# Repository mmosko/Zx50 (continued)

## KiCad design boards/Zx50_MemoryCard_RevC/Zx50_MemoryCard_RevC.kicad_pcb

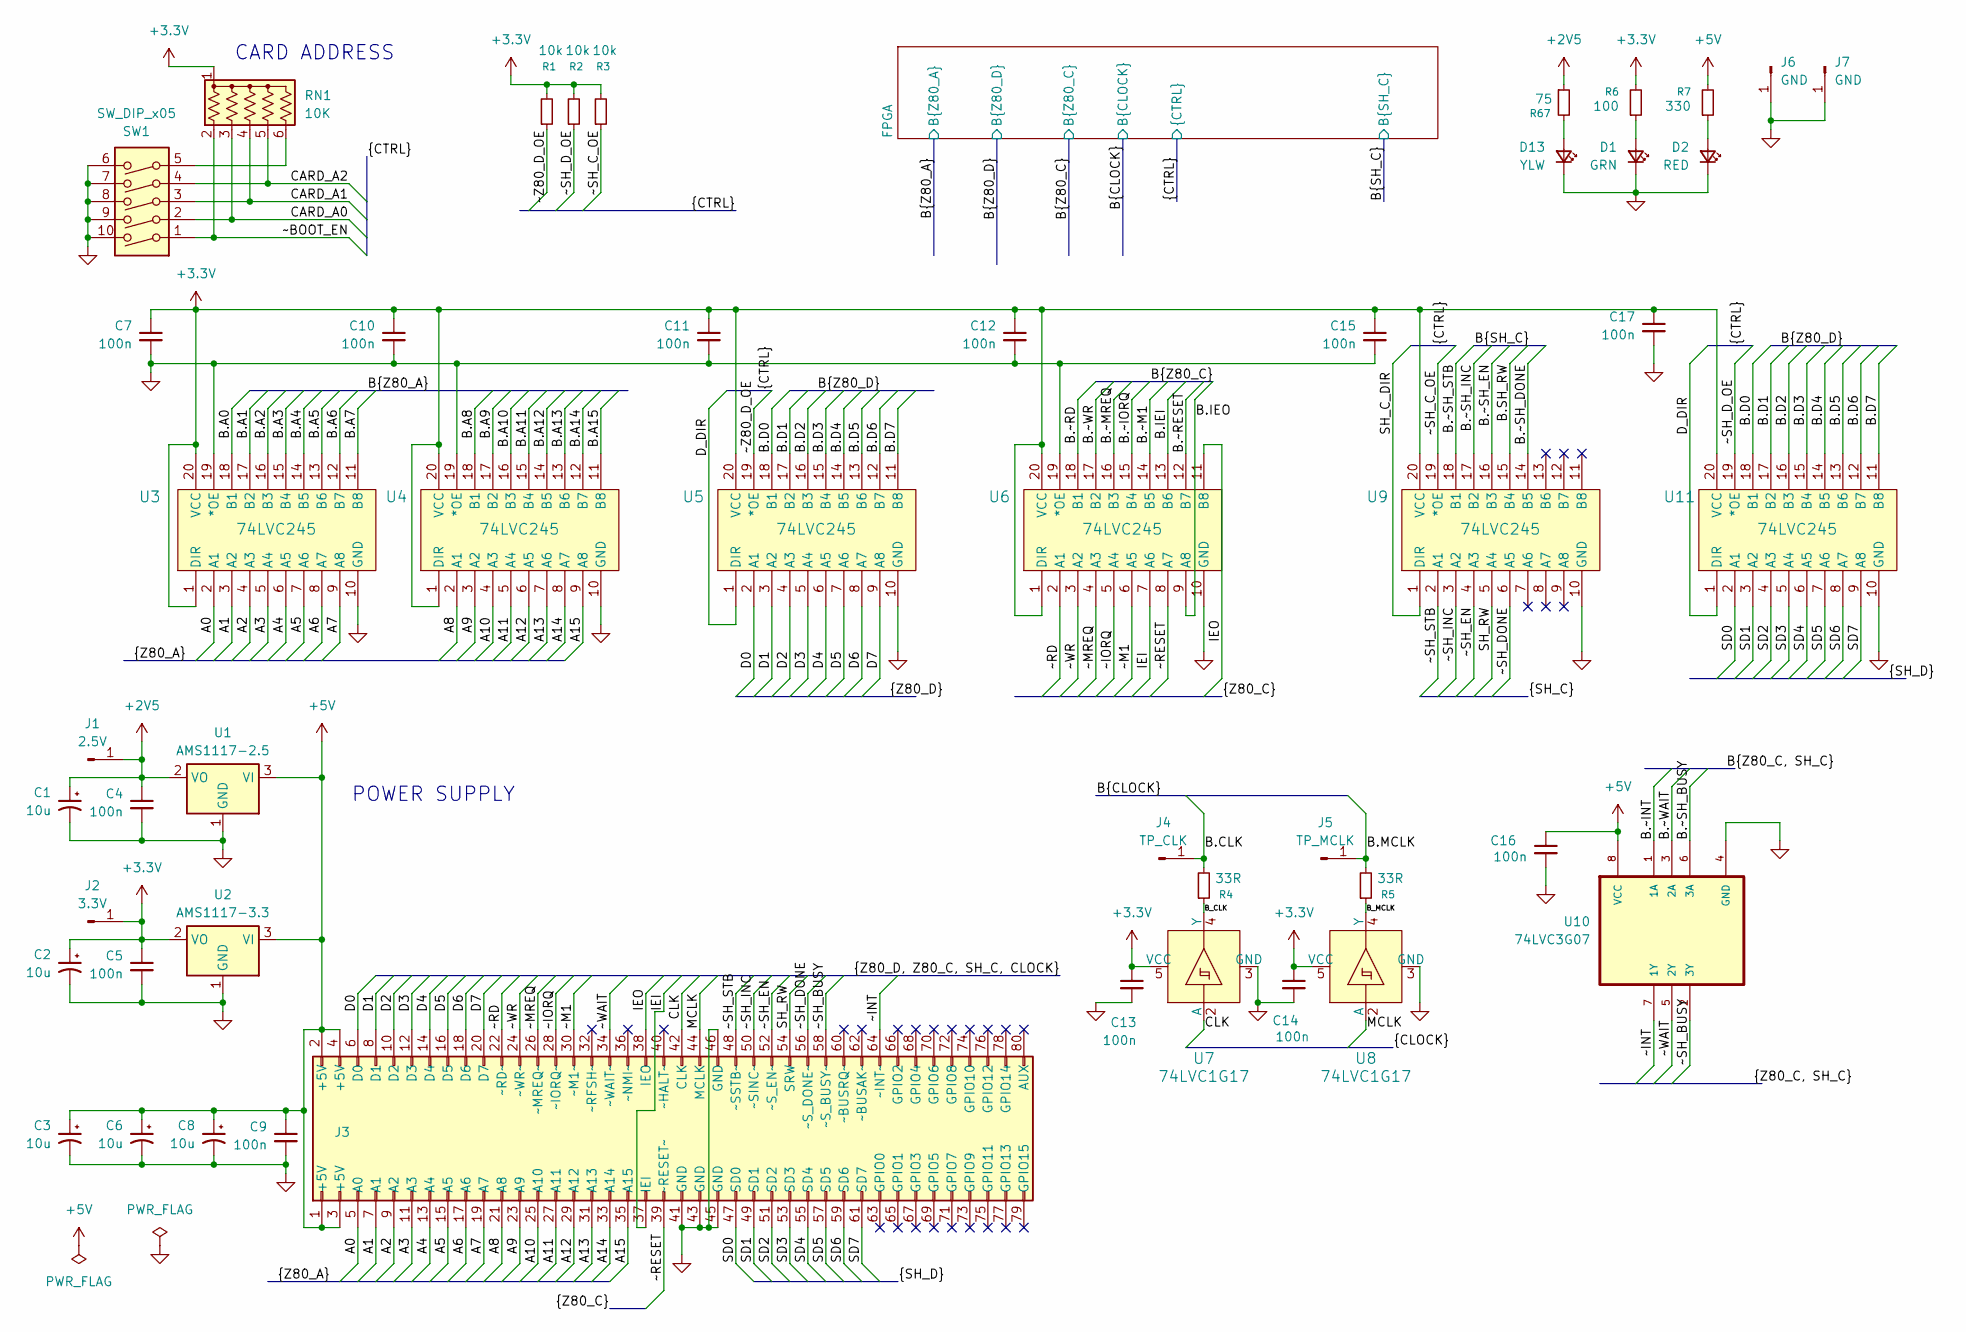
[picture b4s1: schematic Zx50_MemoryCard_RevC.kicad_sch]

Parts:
C1, C2, C3, C6, C8: 10u; C_1206_3216Metric; MFG PN AVX TAJA106K016RNJ Tantalinium; LCSC C7171
C4, C5, C7, C9, C10, C11, C12, C13, C14, C15, C16, C17: 100n; C_0402_1005Metric; LCSC C1525
D1: GRN; LED_0805_2012Metric; MFG_PN KT-0805G; LCSC C2297
D2: RED; LED_0805_2012Metric; MFG_PN NCD0805R1; LCSC C84256
D13: YLW; LED_0805_2012Metric; MFG_PN KT-0805G; LCSC C2297
J1: 2.5V; PinHeader_1x01_P2.54mm_Vertical
J2: 3.3V; PinHeader_1x01_P2.54mm_Vertical
J3: Zx50_EdgeConnector; PinSocket_2x40_P2.54mm_Horizontal_Edge; DigiKey_PN 2057-PH2RA-80-UA-ND
J4: TP_CLK; PinHeader_1x01_P2.54mm_Vertical
J5: TP_MCLK; PinHeader_1x01_P2.54mm_Vertical
J6, J7: GND; PinHeader_1x01_P2.54mm_Vertical
R1, R2, R3: 10k; R_0805_2012Metric; MFG_PN 0805W8F1002T5E; LCSC C17414
R4, R5: 33R; R_0603_1608Metric; MFG_PN 0603WAF330JT5E; LCSC C23140
R6: 100; R_0805_2012Metric; MFG_PN 0805W8F1000T5E; LCSC C17408
R7: 330; R_0805_2012Metric; MFG_PN 0805W8F3300T5E; LCSC C17630
R67: 75; R_0603_1608Metric; MFG_PN 0603WAF750JT5E; LCSC C4275
RN1: 10K; R_Array_SIP6; LCSC 4606X-AP1-103LF
SW1: SW_DIP_x05; SW_DIP_SPSTx05_Slide_9.78x14.88mm_W7.62mm_P2.54mm; LCSC 208-5
U1: AMS1117-2.5; SOT-223-3_TabPin2; Mouser_PN 926-LM1117MPX2.5NOPB
U2: AMS1117-3.3; SOT-223-3_TabPin2; Mouser_PN 926-LM1117MPX3.3NOPB
U3, U4, U5, U6, U9, U11: 74LVC245; TSSOP-20_4.4x6.5mm_P0.65mm; MFG_PART SN74LVC245APWR; LCSC C7848
U7, U8: 74LVC1G17; SOT-753; MPN SN74LVC1G17DBVR; Digi-Key_PN 296-11933-1-ND
U10: 74LVC3G07; VSSOP-8_2.3x2mm_P0.5mm; MFG_PN SN74LVC3G07DCUR; LCSC C131955

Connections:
+2V5: C1.1, C4.1, J1.1, R67.1, U1.2 (VO); also elsewhere on the board
+3.3V: C2.1, C5.1, C7.1, C10.1, C11.1, C12.1, C13.1, C14.1, C15.1, C17.1, J2.1, R1.2, R2.2, R3.2, R6.2, RN1.1 (common), U2.2 (VO), U3.1 (DIR), U3.20 (VCC), U4.1 (DIR), U4.20 (VCC), U5.20 (VCC), U6.1 (DIR), U6.20 (VCC), U7.5 (VCC), U8.5 (VCC), U9.20 (VCC), U11.20 (VCC); also elsewhere on the board
+5V: C3.1, C6.1, C8.1, C9.1, C16.1, J3.1 (+5V), J3.2 (+5V), J3.3 (+5V), J3.4 (+5V), R7.2, U1.3 (VI), U2.3 (VI), U10.8 (VCC); also elsewhere on the board
/A0: J3.5 (A0), U3.2 (A1)
/A1: J3.7 (A1), U3.3 (A2)
/A2: J3.9 (A2), U3.4 (A3)
/A3: J3.11 (A3), U3.5 (A4)
/A4: J3.13 (A4), U3.6 (A5)
/A5: J3.15 (A5), U3.7 (A6)
/A6: J3.17 (A6), U3.8 (A7)
/A7: J3.19 (A7), U3.9 (A8)
/A8: J3.21 (A8), U4.2 (A1)
/A9: J3.23 (A9), U4.3 (A2)
/A10: J3.25 (A10), U4.4 (A3)
/A11: J3.27 (A11), U4.5 (A4)
/A12: J3.29 (A12), U4.6 (A5)
/A13: J3.31 (A13), U4.7 (A6)
/A14: J3.33 (A14), U4.8 (A7)
/A15: J3.35 (A15), U4.9 (A8)
/B.A0: U3.18 (B1)
/B.A1: U3.17 (B2)
/B.A2: U3.16 (B3)
/B.A3: U3.15 (B4)
/B.A4: U3.14 (B5)
/B.A5: U3.13 (B6)
/B.A6: U3.12 (B7)
/B.A7: U3.11 (B8)
/B.A8: U4.18 (B1)
/B.A9: U4.17 (B2)
/B.A10: U4.16 (B3)
/B.A11: U4.15 (B4)
/B.A12: U4.14 (B5)
/B.A13: U4.13 (B6)
/B.A14: U4.12 (B7)
/B.A15: U4.11 (B8)
/B.CLK: J4.1, R4.2; also elsewhere on the board
/B.D0: U5.18 (B1), U11.18 (B1)
/B.D1: U5.17 (B2), U11.17 (B2)
/B.D2: U5.16 (B3), U11.16 (B3)
/B.D3: U5.15 (B4), U11.15 (B4)
/B.D4: U5.14 (B5), U11.14 (B5)
/B.D5: U5.13 (B6), U11.13 (B6)
/B.D6: U5.12 (B7), U11.12 (B7)
/B.D7: U5.11 (B8), U11.11 (B8)
/B.IEI: U6.13 (B6)
/B.IEO: U6.9 (A8)
/B.MCLK: J5.1, R5.2; also elsewhere on the board
/B.SH_RW: U9.15 (B4)
/B.~INT: U10.1 (1A)
/B.~IORQ: U6.15 (B4)
/B.~M1: U6.14 (B5)
/B.~MREQ: U6.16 (B3)
/B.~RD: U6.18 (B1)
/B.~RESET: U6.12 (B7); also elsewhere on the board
/B.~SH_BUSY: U10.6 (3A)
/B.~SH_DONE: U9.14 (B5)
/B.~SH_EN: U9.16 (B3)
/B.~SH_INC: U9.17 (B2)
/B.~SH_STB: U9.18 (B1)
/B.~WAIT: U10.3 (2A)
/B.~WR: U6.17 (B2)
/B_CLK: R4.1, U7.4 (Y)
/B_MCLK: R5.1, U8.4 (Y)
/CARD_A0: RN1.3 (R2), SW1.2
/CARD_A1: RN1.4 (R3), SW1.3
/CARD_A2: RN1.5 (R4), SW1.4
/CLK: J3.42 (CLK), U7.2 (A)
/D0: J3.6 (D0), U5.2 (A1)
/D1: J3.8 (D1), U5.3 (A2)
/D2: J3.10 (D2), U5.4 (A3)
/D3: J3.12 (D3), U5.5 (A4)
/D4: J3.14 (D4), U5.6 (A5)
/D5: J3.16 (D5), U5.7 (A6)
/D6: J3.18 (D6), U5.8 (A7)
/D7: J3.20 (D7), U5.9 (A8)
/D_DIR: U5.1 (DIR), U11.1 (DIR); also elsewhere on the board
/IEI: J3.37 (IEI), U6.7 (A6)
/IEO: J3.38 (IEO), U6.11 (B8)
/MCLK: J3.44 (MCLK), U8.2 (A)
/SD0: J3.47 (SD0), U11.2 (A1)
/SD1: J3.49 (SD1), U11.3 (A2)
/SD2: J3.51 (SD2), U11.4 (A3)
/SD3: J3.53 (SD3), U11.5 (A4)
/SD4: J3.55 (SD4), U11.6 (A5)
/SD5: J3.57 (SD5), U11.7 (A6)
/SD6: J3.59 (SD6), U11.8 (A7)
/SD7: J3.61 (SD7), U11.9 (A8)
/SH_C_DIR: U9.1 (DIR); also elsewhere on the board
/SH_RW: J3.54 (SRW), U9.5 (A4)
/~BOOT_EN: RN1.2 (R1), SW1.1
/~INT: J3.64 (~INT~), U10.7 (1Y)
/~IORQ: J3.28 (~IORQ~), U6.5 (A4)
/~M1: J3.30 (~M1~), U6.6 (A5)
/~MREQ: J3.26 (~MREQ~), U6.4 (A3)
/~RD: J3.22 (~RD~), U6.2 (A1)
/~RESET: J3.39 (~RESET~), U6.8 (A7)
/~SH_BUSY: J3.58 (~S_BUSY~), U10.2 (3Y)
/~SH_C_OE: R3.1, U9.19 (*OE); also elsewhere on the board
/~SH_DONE: J3.56 (~S_DONE~), U9.6 (A5)
/~SH_D_OE: R2.1, U11.19 (*OE); also elsewhere on the board
/~SH_EN: J3.52 (~S_EN~), U9.4 (A3)
/~SH_INC: J3.50 (~SINC~), U9.3 (A2)
/~SH_STB: J3.48 (~SSTB~), U9.2 (A1)
/~WAIT: J3.34 (~WAIT~), U10.5 (2Y)
/~WR: J3.24 (~WR~), U6.3 (A2)
/~Z80_D_OE: R1.1, U5.19 (*OE); also elsewhere on the board
GND: C1.2, C2.2, C3.2, C4.2, C5.2, C6.2, C7.2, C8.2, C9.2, C10.2, C11.2, C12.2, C13.2, C14.2, C15.2, C16.2, C17.2, D1.1 (K), D2.1 (K), D13.1 (K), J3.41 (GND), J3.43 (GND), J3.45 (GND), J3.46 (GND), J6.1, J7.1, SW1.6, SW1.7, SW1.8, SW1.9, SW1.10, U1.1 (GND), U2.1 (GND), U3.10 (GND), U3.19 (*OE), U4.10 (GND), U4.19 (*OE), U5.10 (GND), U6.10 (GND), U6.19 (*OE), U7.3 (GND), U8.3 (GND), U9.10 (GND), U10.4 (GND), U11.10 (GND); also elsewhere on the board
unnamed: D1.2 (A), R6.1
unnamed: D2.2 (A), R7.1
unnamed: D13.2 (A), R67.2
unnamed: RN1.6 (R5), SW1.5

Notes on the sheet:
CARD ADDRESS
POWER SUPPLY

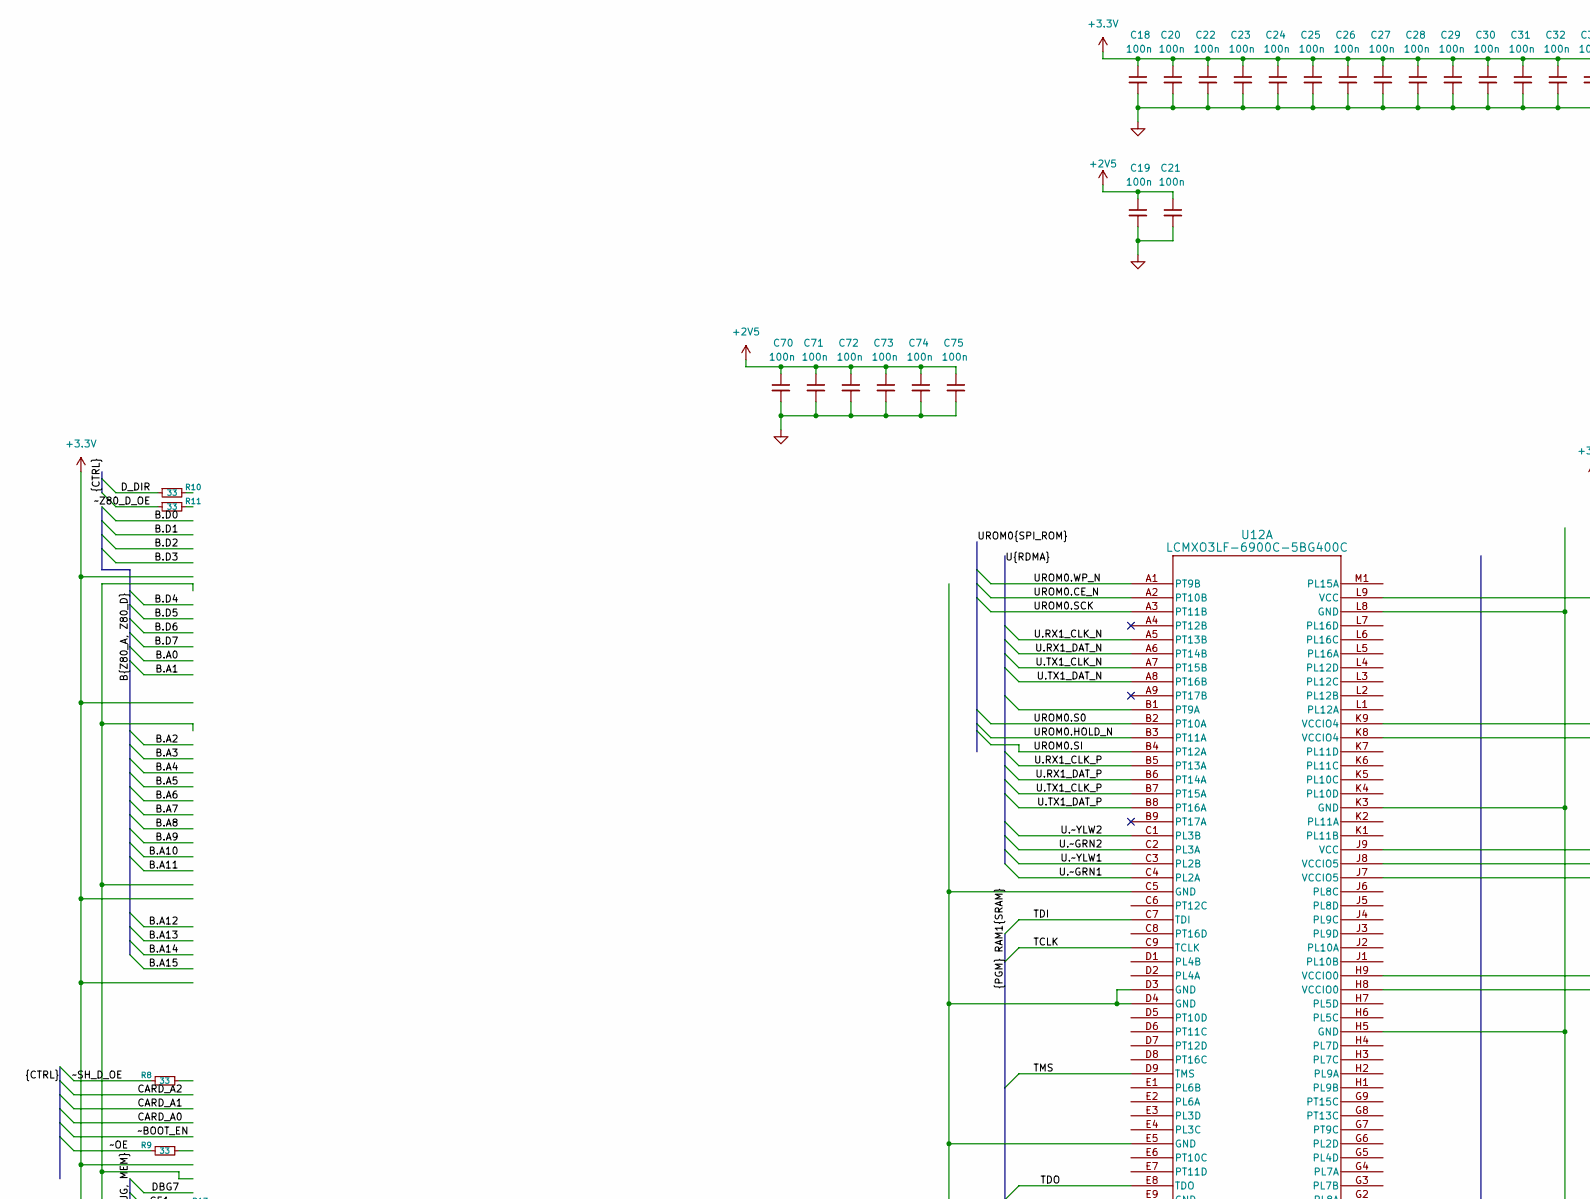
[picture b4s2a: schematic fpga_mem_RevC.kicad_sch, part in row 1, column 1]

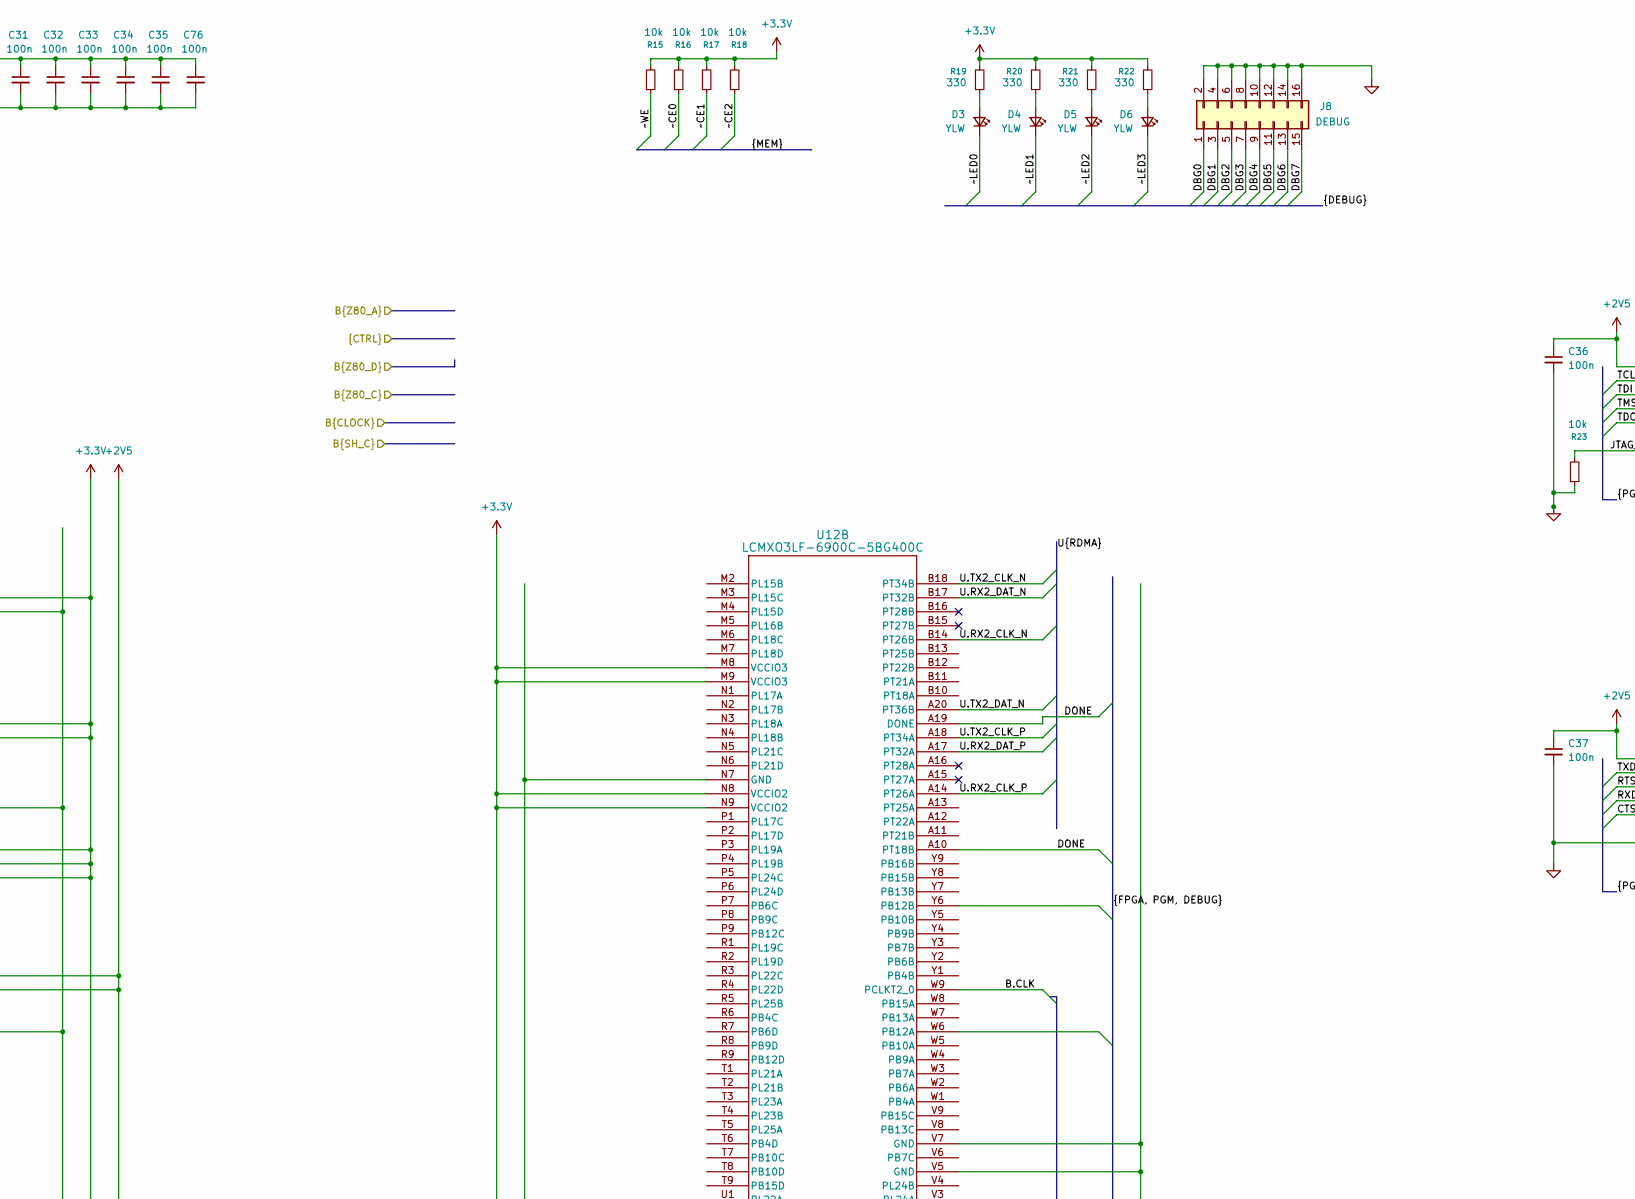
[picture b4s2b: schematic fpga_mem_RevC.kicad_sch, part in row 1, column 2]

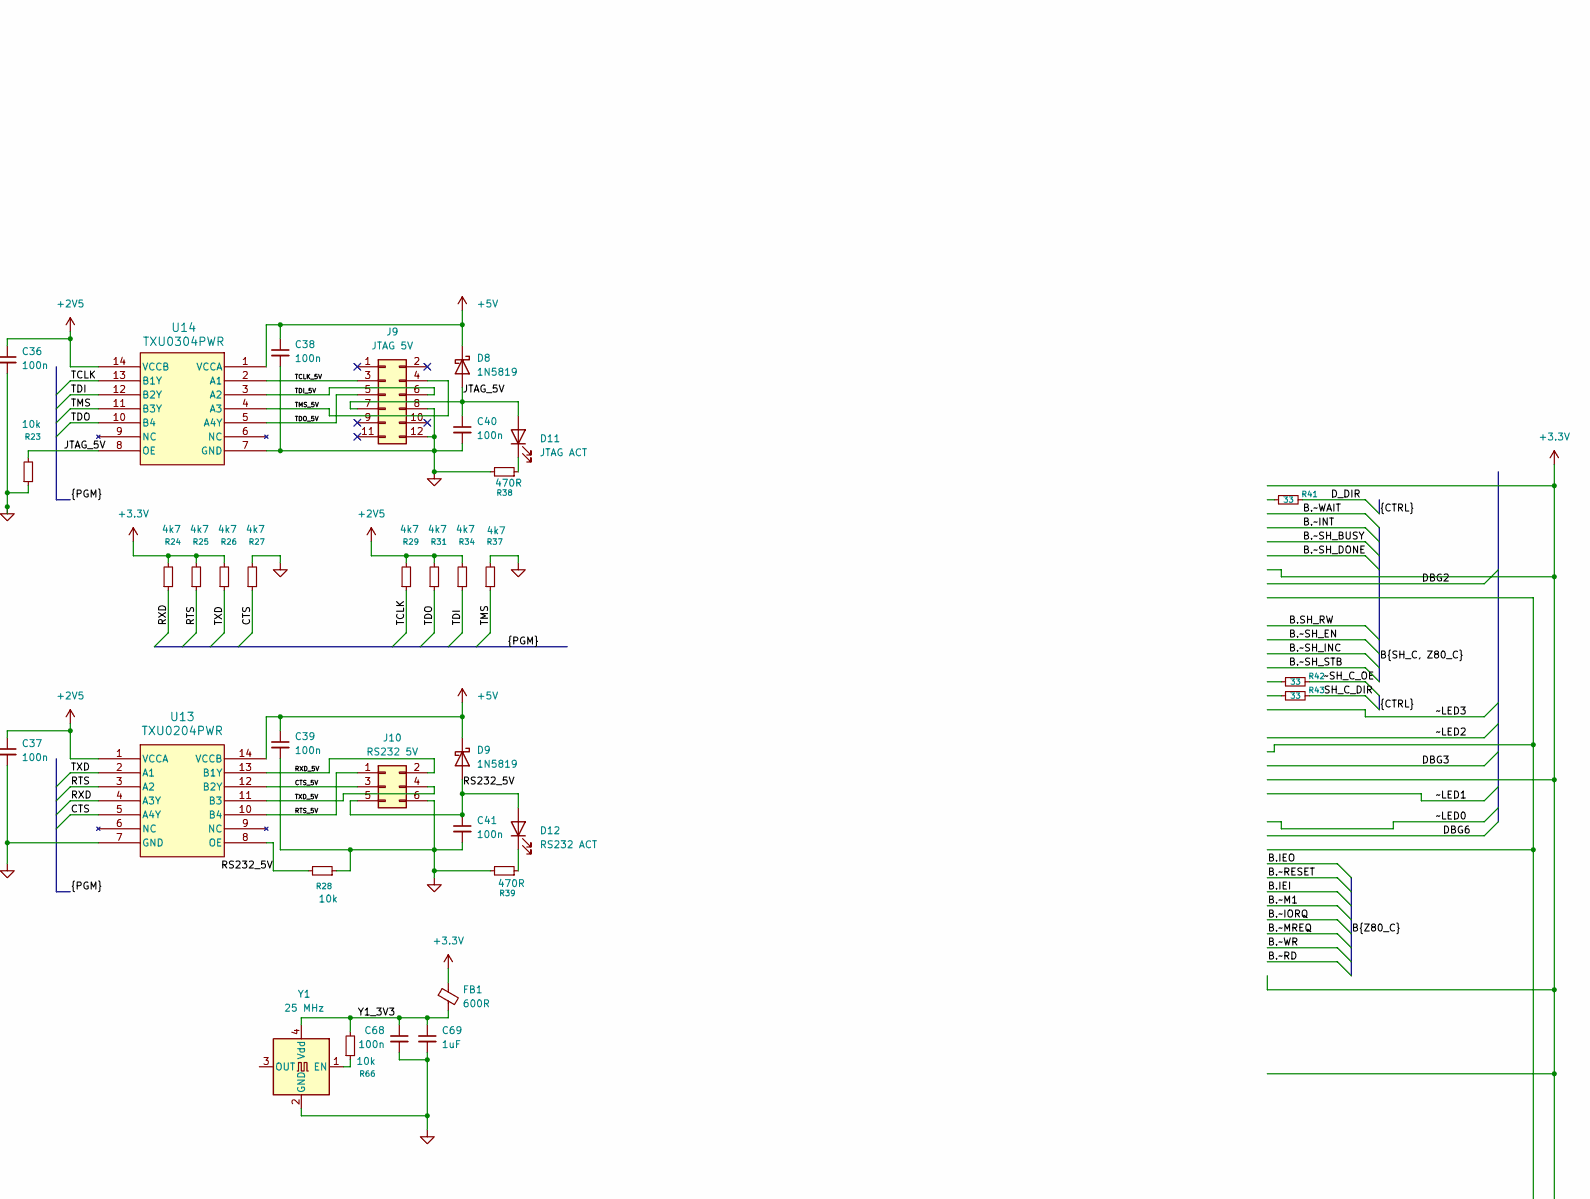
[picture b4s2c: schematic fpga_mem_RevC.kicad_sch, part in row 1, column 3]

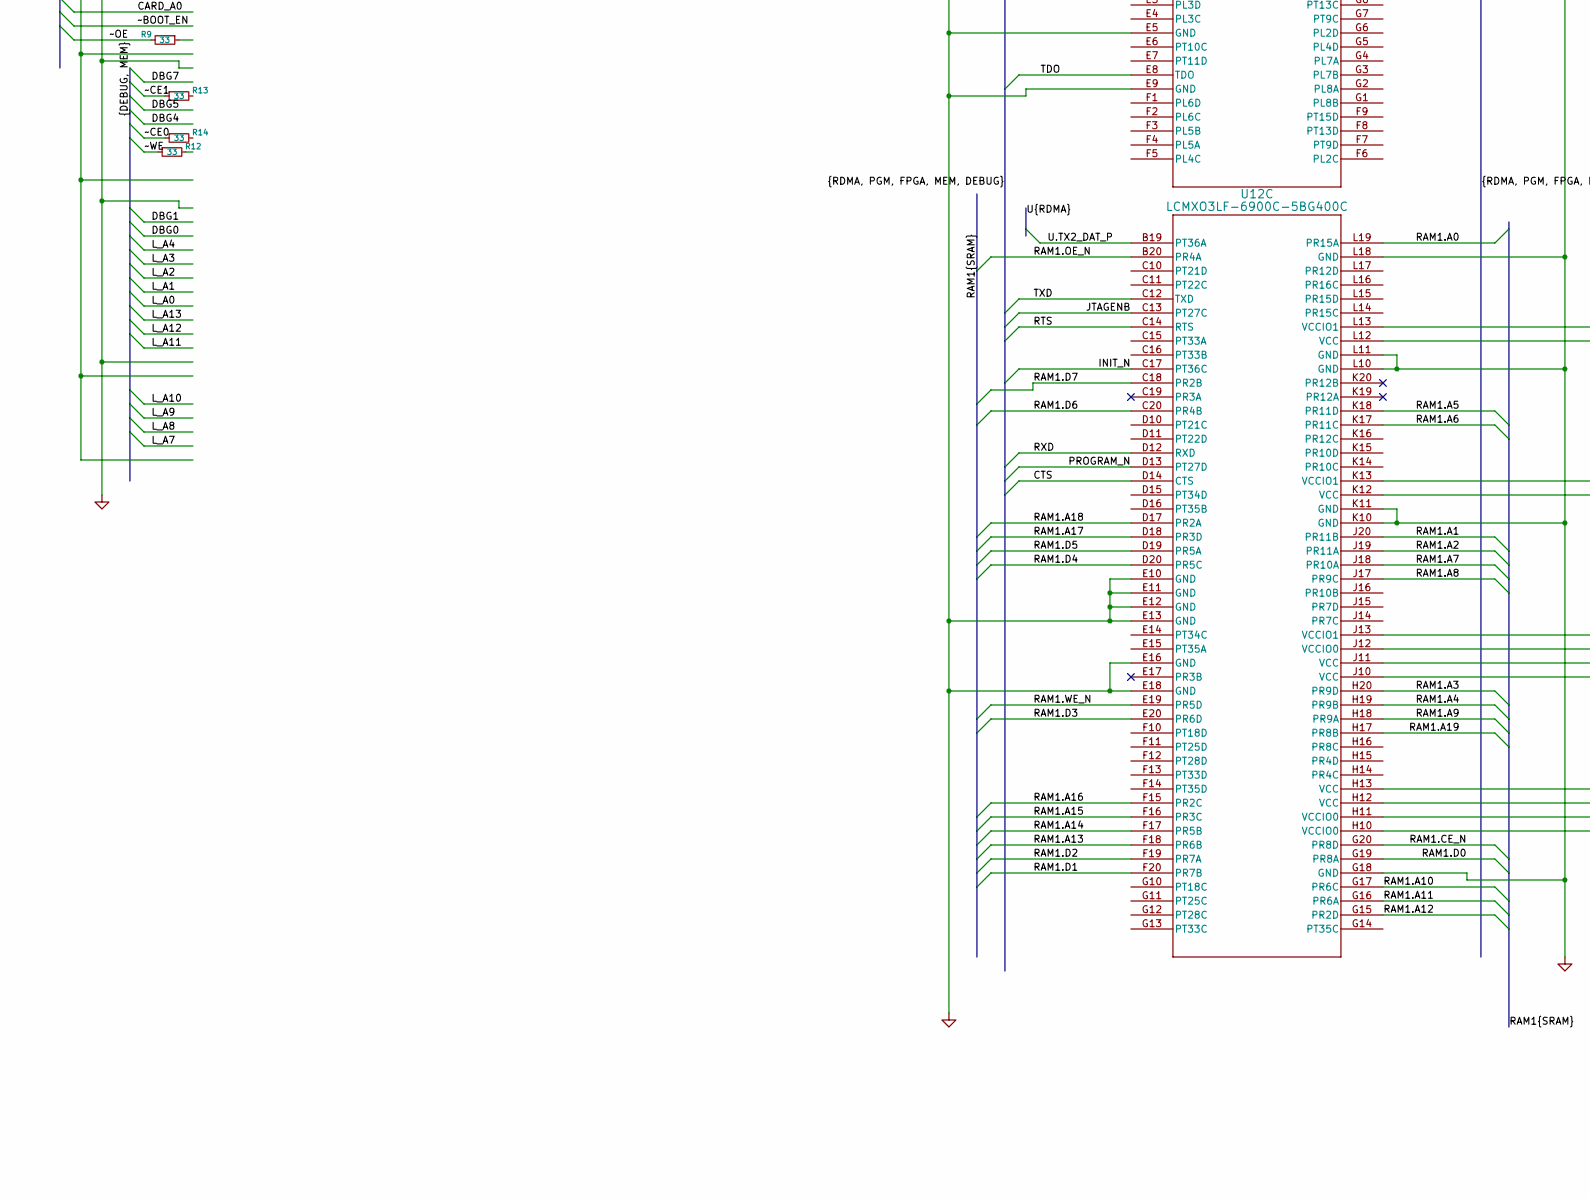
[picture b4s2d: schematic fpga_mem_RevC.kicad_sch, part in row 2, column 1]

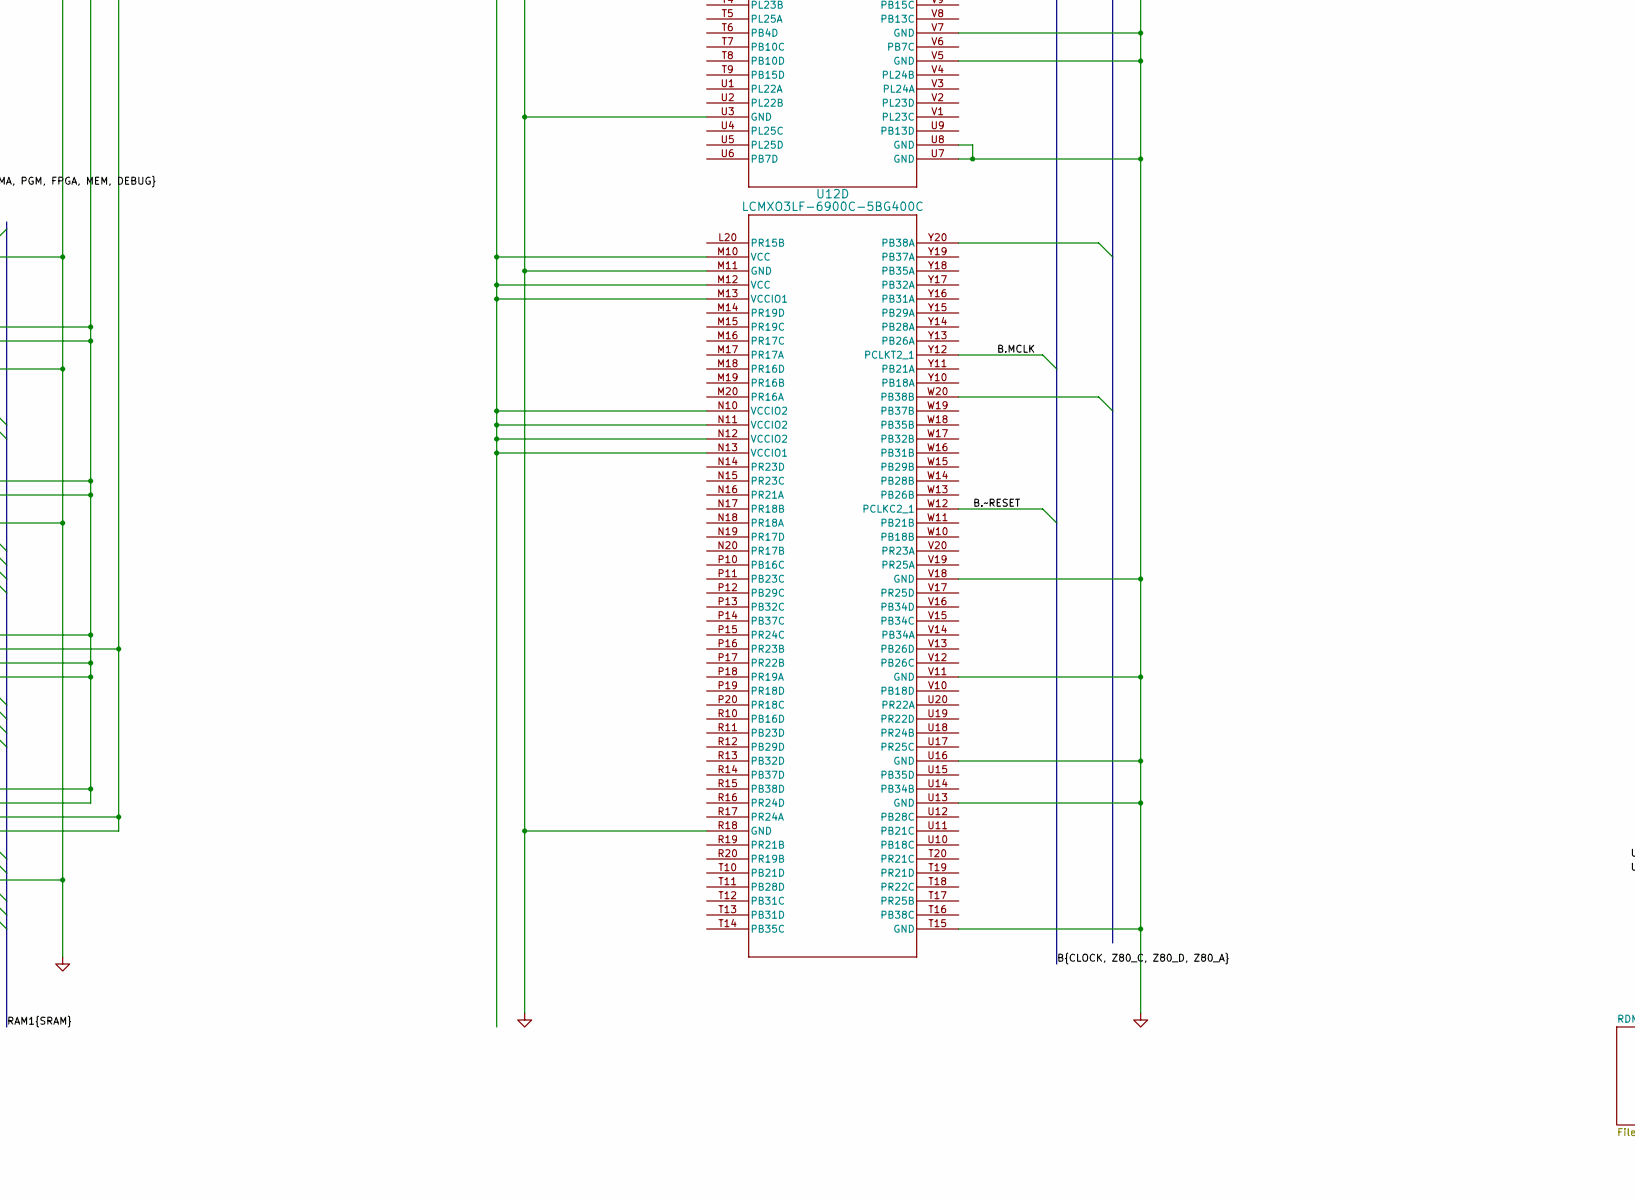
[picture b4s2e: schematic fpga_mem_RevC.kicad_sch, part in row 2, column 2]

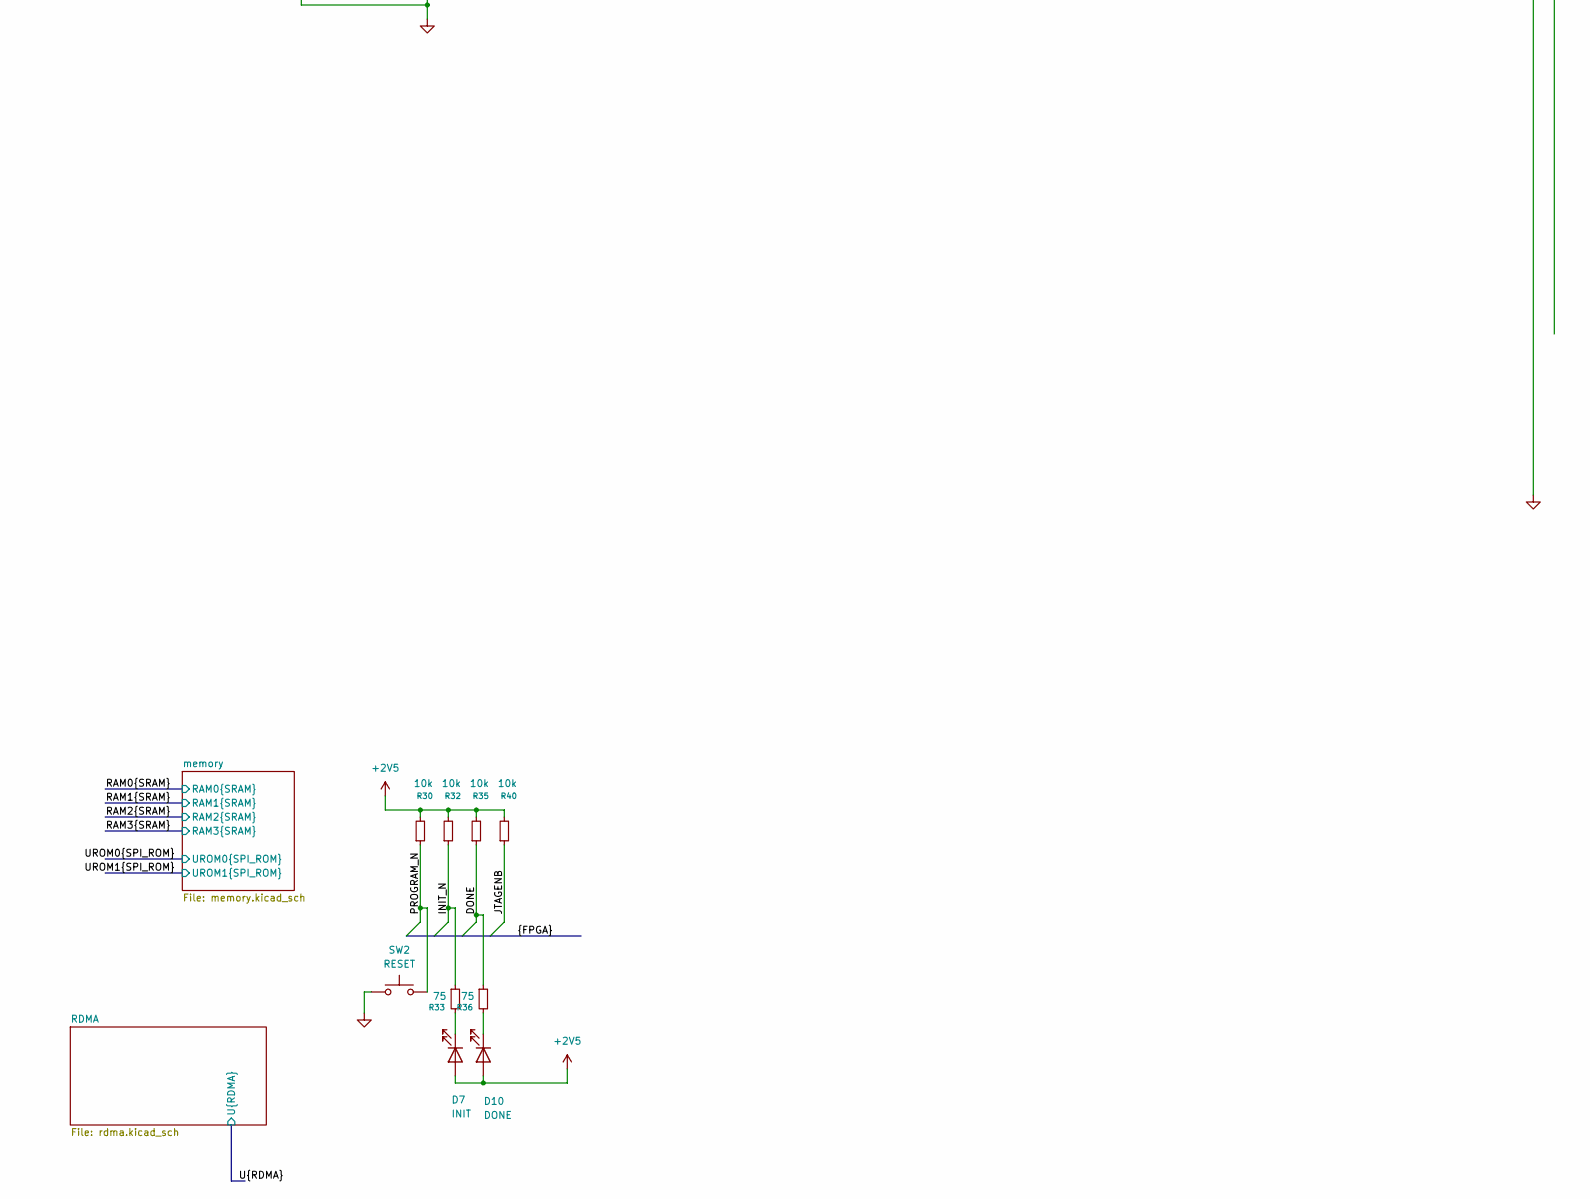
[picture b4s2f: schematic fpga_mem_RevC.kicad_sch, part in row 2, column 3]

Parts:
C18, C19, C20, C21, C22, C23, C24, C25, C26, C27, C28, C29, C30, C31, C32, C33, C34, C35, C36, C37, C38, C39, C40, C41, C68, C70, C71, C72, C73, C74, C75, C76: 100n; C_0402_1005Metric; LCSC C1525
C69: 1uF; C_0402_1005Metric; LCSC C52923
D3, D4, D5, D6: YLW; LED_0805_2012Metric; MFG_PN KT-0805Y; LCSC C2296
D7: INIT; LED_D3.0mm
D8, D9: 1N5819; D_SOD-323; LCSC C191023
D10: DONE; LED_D3.0mm
D11: JTAG ACT; LED_D3.0mm
D12: RS232 ACT; LED_D3.0mm
FB1: 600R; 0805; LCSC C1017
J8: DEBUG; IDC-Header_2x08_P2.54mm_Vertical
J9: JTAG 5V; IDC-Header_2x06_P2.54mm_Horizontal
J10: RS232 5V; IDC-Header_2x03_P2.54mm_Horizontal
R8, R9, R10, R11, R12, R13, R14, R41, R42, R43: 33; R_0402_1005Metric; MFG_PN 0402WGF1000TCE; LCSC C25076
R15, R16, R17, R18: 10k; R_0402_1005Metric; MFG_PN 0402W8F1002T5E; LCSC C25744
R19, R20, R21, R22: 330; R_0805_2012Metric; MFG_PN 0805W8F3300T5E; LCSC C17630
R23, R28, R30, R32, R35, R40, R66: 10k; R_0402_1005Metric; MFG_PN 0402WGF1002TCE; LCSC C25744
R24, R25, R26, R27, R29, R31, R34, R37: 4k7; R_0402_1005Metric; MFG_PN 0402WGF4701TCE; LCSC C25900
R33, R36: 75; R_0603_1608Metric; MFG_PN 0603WAF750JT5E; LCSC C4275
R38, R39: 470R; R_0805_2012Metric; MFG_PN 0805W8F4700T5E; LCSC C17710
SW2: RESET; SW_PUSH_6mm_H7.3mm; DigiKey_PN SW402-ND
U12: LCMXO3LF-6900C-5BG400C; CABGA400_LAT
U13: TXU0204PWR; TSSOP14_PW_TEX; LCSC C4363888
U14: TXU0304PWR; TSSOP14_PW_TEX; LCSC C4364118
Y1: 25 MHz; Crystal_SMD_3225-4Pin_3.2x2.5mm; LCSC C669088

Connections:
+2V5: C19.1, C21.1, C36.1, C37.1, C70.1, C71.1, C72.1, C73.1, C74.1, C75.1, D7.2 (A), D10.2 (A), R29.2, R30.2, R31.2, R32.2, R34.2, R35.2, R40.2, U12.H8 (VCCIO0), U12.H9 (VCCIO0), U12.H10 (VCCIO0), U12.H11 (VCCIO0), U12.J12 (VCCIO0), U13.1 (VCCA), U14.14 (VCCB); also elsewhere on the board
+3.3V: C18.1, C20.1, C22.1, C23.1, C24.1, C25.1, C26.1, C27.1, C28.1, C29.1, C30.1, C31.1, C32.1, C33.1, C34.1, C35.1, C76.1, FB1.1, R15.2, R16.2, R17.2, R18.2, R19.2, R20.2, R21.2, R22.2, R24.2, R25.2, R26.2, U12.H12 (VCC), U12.H13 (VCC), U12.J7 (VCCIO5), U12.J8 (VCCIO5), U12.J9 (VCC), U12.J10 (VCC), U12.J11 (VCC), U12.J13 (VCCIO1), U12.K8 (VCCIO4), U12.K9 (VCCIO4), U12.K12 (VCC), U12.K13 (VCCIO1), U12.L9 (VCC), U12.L12 (VCC), U12.L13 (VCCIO1), U12.M8 (VCCIO3), U12.M9 (VCCIO3), U12.M10 (VCC), U12.M12 (VCC), U12.M13 (VCCIO1), U12.N8 (VCCIO2), U12.N9 (VCCIO2), U12.N10 (VCCIO2), U12.N11 (VCCIO2), U12.N12 (VCCIO2), U12.N13 (VCCIO1); also elsewhere on the board
+5V: C38.1, C39.1, D8.1 (K), D9.1 (K), U13.14 (VCCB), U14.1 (VCCA); also elsewhere on the board
/B.CLK: U12.W9 (PCLKT2_0); also elsewhere on the board
/B.MCLK: U12.Y12 (PCLKT2_1); also elsewhere on the board
/B.~RESET: U12.W12 (PCLKC2_1); also elsewhere on the board
/D_DIR: R10.1, R41.2; also elsewhere on the board
/FPGA/CTS: R27.1, U12.D14 (CTS), U13.5 (A4Y)
/FPGA/CTS_5V: J10.3, U13.12 (B2Y)
/FPGA/DBG0: J8.1
/FPGA/DBG1: J8.3
/FPGA/DBG2: J8.5
/FPGA/DBG3: J8.7
/FPGA/DBG4: J8.9
/FPGA/DBG5: J8.11
/FPGA/DBG6: J8.13
/FPGA/DBG7: J8.15
/FPGA/DONE: R35.1, R36.1, U12.A10 (PT18B), U12.A19 (DONE)
/FPGA/INIT_N: R32.1, R33.1, U12.C17 (PT36C)
/FPGA/JTAGENB: R40.1, U12.C13 (PT27C)
/FPGA/JTAG_5V: C40.1, D8.2 (A), D11.2 (A), J9.7, R23.2, U14.8 (OE)
/FPGA/PROGRAM_N: R30.1, SW2.2, U12.D13 (PT27D)
/FPGA/RAM1.A0: U12.L19 (PR15A); also elsewhere on the board
/FPGA/RAM1.A1: U12.J20 (PR11B); also elsewhere on the board
/FPGA/RAM1.A2: U12.J19 (PR11A); also elsewhere on the board
/FPGA/RAM1.A3: U12.H20 (PR9D); also elsewhere on the board
/FPGA/RAM1.A4: U12.H19 (PR9B); also elsewhere on the board
/FPGA/RAM1.A5: U12.K18 (PR11D); also elsewhere on the board
/FPGA/RAM1.A6: U12.K17 (PR11C); also elsewhere on the board
/FPGA/RAM1.A7: U12.J18 (PR10A); also elsewhere on the board
/FPGA/RAM1.A8: U12.J17 (PR9C); also elsewhere on the board
/FPGA/RAM1.A9: U12.H18 (PR9A); also elsewhere on the board
/FPGA/RAM1.A10: U12.G17 (PR6C); also elsewhere on the board
/FPGA/RAM1.A11: U12.G16 (PR6A); also elsewhere on the board
/FPGA/RAM1.A12: U12.G15 (PR2D); also elsewhere on the board
/FPGA/RAM1.A13: U12.F18 (PR6B); also elsewhere on the board
/FPGA/RAM1.A14: U12.F17 (PR5B); also elsewhere on the board
/FPGA/RAM1.A15: U12.F16 (PR3C); also elsewhere on the board
/FPGA/RAM1.A16: U12.F15 (PR2C); also elsewhere on the board
/FPGA/RAM1.A17: U12.D18 (PR3D); also elsewhere on the board
/FPGA/RAM1.A18: U12.D17 (PR2A); also elsewhere on the board
/FPGA/RAM1.A19: U12.H17 (PR8B); also elsewhere on the board
/FPGA/RAM1.CE_N: U12.G20 (PR8D); also elsewhere on the board
/FPGA/RAM1.D0: U12.G19 (PR8A); also elsewhere on the board
/FPGA/RAM1.D1: U12.F20 (PR7B); also elsewhere on the board
/FPGA/RAM1.D2: U12.F19 (PR7A); also elsewhere on the board
/FPGA/RAM1.D3: U12.E20 (PR6D); also elsewhere on the board
/FPGA/RAM1.D4: U12.D20 (PR5C); also elsewhere on the board
/FPGA/RAM1.D5: U12.D19 (PR5A); also elsewhere on the board
/FPGA/RAM1.D6: U12.C20 (PR4B); also elsewhere on the board
/FPGA/RAM1.D7: U12.C18 (PR2B); also elsewhere on the board
/FPGA/RAM1.OE_N: U12.B20 (PR4A); also elsewhere on the board
/FPGA/RAM1.WE_N: U12.E19 (PR5D); also elsewhere on the board
/FPGA/RS232_5V: C41.1, D9.2 (A), D12.2 (A), J10.5, R28.2, U13.8 (OE)
/FPGA/RTS: R25.1, U12.C14 (RTS), U13.3 (A2)
/FPGA/RTS_5V: J10.1, U13.10 (B4)
/FPGA/RXD: R24.1, U12.D12 (RXD), U13.4 (A3Y)
/FPGA/RXD_5V: J10.2, U13.13 (B1Y)
/FPGA/TCLK: R29.1, U12.C9 (TCLK), U14.13 (B1Y)
/FPGA/TCLK_5V: J9.3, U14.2 (A1)
/FPGA/TDI: R34.1, U12.C7 (TDI), U14.12 (B2Y)
/FPGA/TDI_5V: J9.6, U14.3 (A2)
/FPGA/TDO: R31.1, U12.E8 (TDO), U14.10 (B4)
/FPGA/TDO_5V: J9.5, U14.5 (A4Y)
/FPGA/TMS: R37.1, U12.D9 (TMS), U14.11 (B3Y)
/FPGA/TMS_5V: J9.4, U14.4 (A3)
/FPGA/TXD: R26.1, U12.C12 (TXD), U13.2 (A1)
/FPGA/TXD_5V: J10.4, U13.11 (B3)
/FPGA/U.RX1_CLK_N: U12.A5 (PT13B); also elsewhere on the board
/FPGA/U.RX1_CLK_P: U12.B5 (PT13A); also elsewhere on the board
/FPGA/U.RX1_DAT_N: U12.A6 (PT14B); also elsewhere on the board
/FPGA/U.RX1_DAT_P: U12.B6 (PT14A); also elsewhere on the board
/FPGA/U.RX2_CLK_N: U12.B14 (PT26B); also elsewhere on the board
/FPGA/U.RX2_CLK_P: U12.A14 (PT26A); also elsewhere on the board
/FPGA/U.RX2_DAT_N: U12.B17 (PT32B); also elsewhere on the board
/FPGA/U.RX2_DAT_P: U12.A17 (PT32A); also elsewhere on the board
/FPGA/U.TX1_CLK_N: U12.A7 (PT15B); also elsewhere on the board
/FPGA/U.TX1_CLK_P: U12.B7 (PT15A); also elsewhere on the board
/FPGA/U.TX1_DAT_N: U12.A8 (PT16B); also elsewhere on the board
/FPGA/U.TX1_DAT_P: U12.B8 (PT16A); also elsewhere on the board
/FPGA/U.TX2_CLK_N: U12.B18 (PT34B); also elsewhere on the board
/FPGA/U.TX2_CLK_P: U12.A18 (PT34A); also elsewhere on the board
/FPGA/U.TX2_DAT_N: U12.A20 (PT36B); also elsewhere on the board
/FPGA/U.TX2_DAT_P: U12.B19 (PT36A); also elsewhere on the board
/FPGA/U.~GRN1: U12.C4 (PL2A); also elsewhere on the board
/FPGA/U.~GRN2: U12.C2 (PL3A); also elsewhere on the board
/FPGA/U.~YLW1: U12.C3 (PL2B); also elsewhere on the board
/FPGA/U.~YLW2: U12.C1 (PL3B); also elsewhere on the board
/FPGA/UROM0.CE_N: U12.A2 (PT10B); also elsewhere on the board
/FPGA/UROM0.HOLD_N: U12.B3 (PT11A)
/FPGA/UROM0.S0: U12.B2 (PT10A)
/FPGA/UROM0.SCK: U12.A3 (PT11B); also elsewhere on the board
/FPGA/UROM0.SI: U12.B4 (PT12A); also elsewhere on the board
/FPGA/UROM0.WP_N: U12.A1 (PT9B); also elsewhere on the board
/FPGA/Y1_3V3: C68.1, C69.1, FB1.2, R66.2, Y1.4 (Vdd)
/FPGA/~CE0: R14.1, R16.1
/FPGA/~CE1: R13.1, R17.1
/FPGA/~CE2: R18.1
/FPGA/~LED0: D3.1 (K)
/FPGA/~LED1: D4.1 (K)
/FPGA/~LED2: D5.1 (K)
/FPGA/~LED3: D6.1 (K)
/FPGA/~OE: R9.2
/FPGA/~WE: R12.1, R15.1
/SH_C_DIR: R43.2; also elsewhere on the board
/~SH_C_OE: R42.2; also elsewhere on the board
/~SH_D_OE: R8.2; also elsewhere on the board
/~Z80_D_OE: R11.1; also elsewhere on the board
GND: C18.2, C19.2, C20.2, C21.2, C22.2, C23.2, C24.2, C25.2, C26.2, C27.2, C28.2, C29.2, C30.2, C31.2, C32.2, C33.2, C34.2, C35.2, C36.2, C37.2, C38.2, C39.2, C40.2, C41.2, C68.2, C69.2, C70.2, C71.2, C72.2, C73.2, C74.2, C75.2, C76.2, J8.2, J8.4, J8.6, J8.8, J8.10, J8.12, J8.14, J8.16, J9.8, J9.12, J10.6, R23.1, R27.2, R28.1, R37.2, R38.2, R39.2, SW2.1, U12.C5 (GND), U12.D3 (GND), U12.D4 (GND), U12.E5 (GND), U12.E9 (GND), U12.E10 (GND), U12.E11 (GND), U12.E12 (GND), U12.E13 (GND), U12.E16 (GND), U12.E18 (GND), U12.G18 (GND), U12.H5 (GND), U12.K3 (GND), U12.K10 (GND), U12.K11 (GND), U12.L8 (GND), U12.L10 (GND), U12.L11 (GND), U12.L18 (GND), U12.M11 (GND), U12.N7 (GND), U12.R18 (GND), U12.T15 (GND), U12.U3 (GND), U12.U7 (GND), U12.U8 (GND), U12.U13 (GND), U12.U16 (GND), U12.V5 (GND), U12.V7 (GND), U12.V11 (GND), U12.V18 (GND), U13.7 (GND), U14.7 (GND), Y1.2 (GND); also elsewhere on the board
unnamed: D3.2 (A), R19.1
unnamed: D4.2 (A), R20.1
unnamed: D5.2 (A), R21.1
unnamed: D6.2 (A), R22.1
unnamed: D7.1 (K), R33.2
unnamed: D10.1 (K), R36.2
unnamed: D11.1 (K), R38.1
unnamed: D12.1 (K), R39.1
unnamed: R66.1, Y1.1 (EN)
